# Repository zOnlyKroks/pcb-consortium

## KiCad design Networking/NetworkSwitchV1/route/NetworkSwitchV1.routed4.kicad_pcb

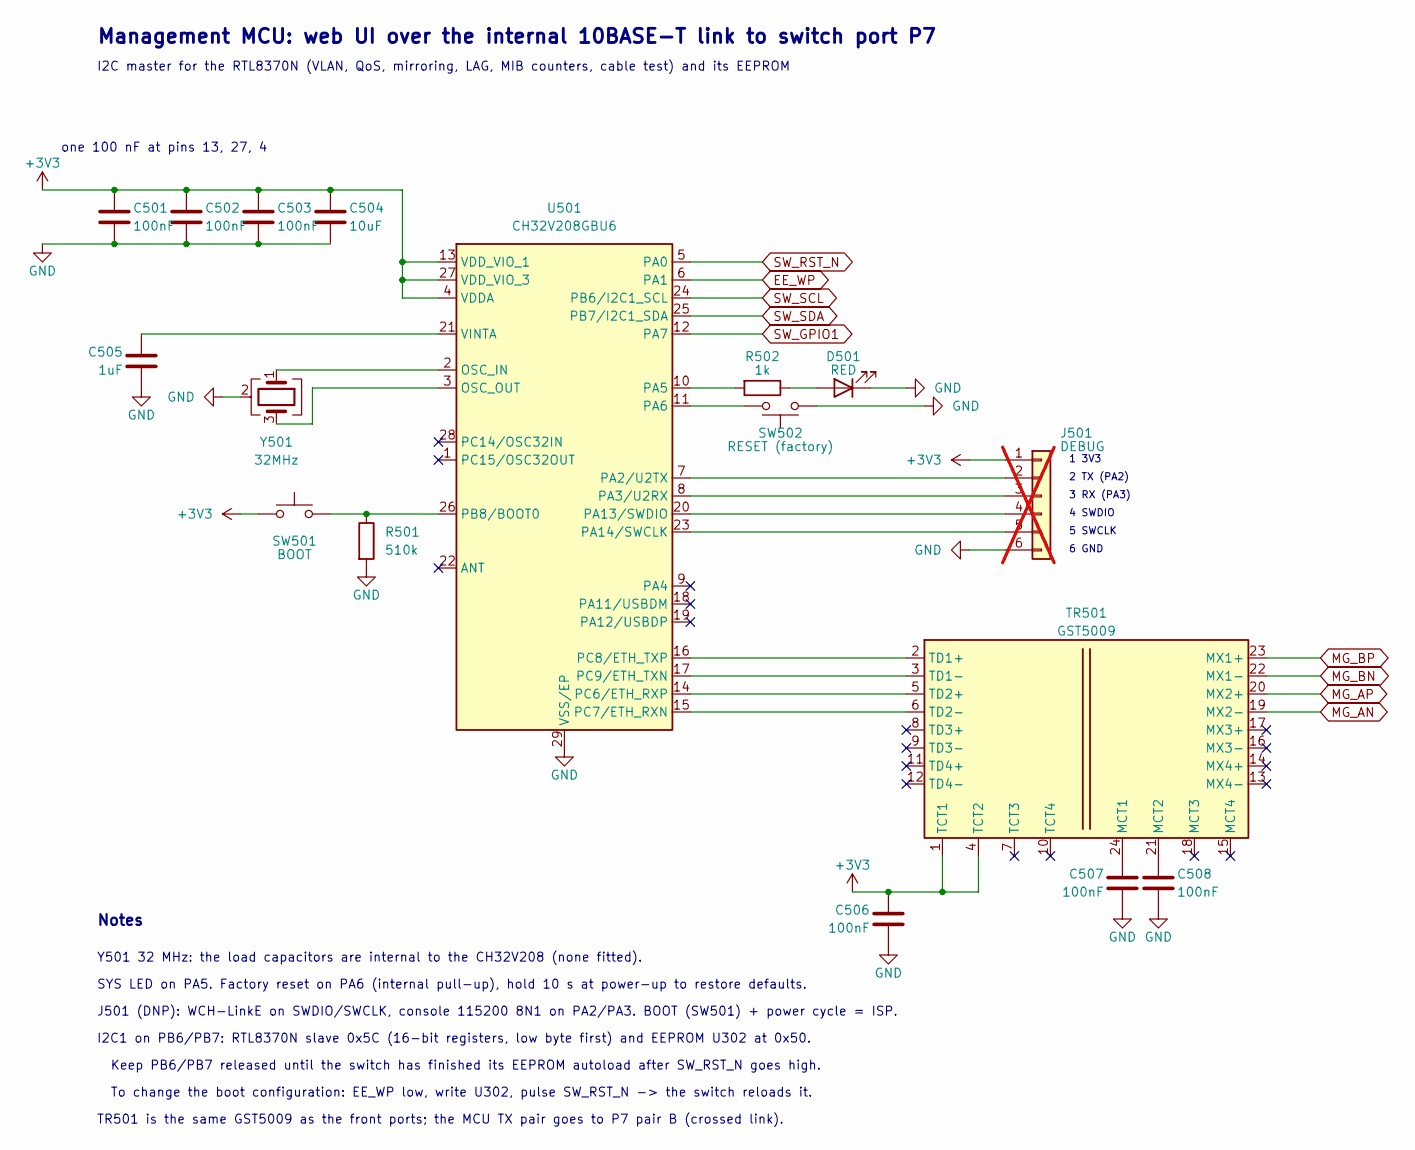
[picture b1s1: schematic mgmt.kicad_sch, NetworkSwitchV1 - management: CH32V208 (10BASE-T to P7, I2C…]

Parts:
C501, C502, C503, C506, C507, C508: 100nF; C_0603_1608Metric; LCSC Part # C14663
C504: 10uF; C_0603_1608Metric; LCSC Part # C19702
C505: 1uF; C_0603_1608Metric; LCSC Part # C15849
D501: RED; LED_0603_1608Metric; LCSC Part # C2286
J501: DEBUG; PinHeader_1x06_P2.54mm_Vertical; LCSC Part # C492405; not fitted
R501: 510k; R_0603_1608Metric; LCSC Part # C23192
R502: 1k; R_0603_1608Metric; LCSC Part # C21190
SW501: BOOT; SW-SMD_4P-L5.1-W5.1-P3.70-LS6.5-TL_H1.5; LCSC Part # C318884
SW502: RESET (factory); SW-SMD_4P-L5.1-W5.1-P3.70-LS6.5-TL_H1.5; LCSC Part # C318884
TR501: GST5009; XFMR-SMD_24P-L15.1-W7.1-P1.00-LS9.7-BL; LCSC Part # C55213474
U501: CH32V208GBU6; QFN-28_L4.0-W4.0-P0.40-BL-EP2.8; LCSC Part # C7434833
Y501: 32MHz; Crystal_SMD_3225-4Pin_3.2x2.5mm; MPN X322532MOB4SI; LCSC Part # C9009

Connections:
+3V3: C501.1, C502.1, C503.1, C504.1, C506.1, J501.1, SW501.1, SW501.2 (1), TR501.1 (TCT1), TR501.4 (TCT2), U501.4 (VDDA), U501.13 (VDD_VIO_1), U501.27 (VDD_VIO_3); also elsewhere on the board
EE_WP: U501.6 (PA1); also elsewhere on the board
GND: C501.2, C502.2, C503.2, C504.2, C505.2, C506.2, C507.2, C508.2, D501.1 (K), J501.6, R501.2, SW502.1, SW502.2 (1), U501.29 (VSS/EP), Y501.2 (G), Y501.4 (G); also elsewhere on the board
MG_AN: TR501.19 (MX2-); also elsewhere on the board
MG_AP: TR501.20 (MX2+); also elsewhere on the board
MG_BN: TR501.22 (MX1-); also elsewhere on the board
MG_BP: TR501.23 (MX1+); also elsewhere on the board
unnamed: D501.2 (A), R502.1
unnamed: J501.2, U501.7 (PA2/U2TX)
unnamed: J501.3, U501.8 (PA3/U2RX)
unnamed: J501.4, U501.20 (PA13/SWDIO)
unnamed: J501.5, U501.23 (PA14/SWCLK)
unnamed: C507.1, TR501.24 (MCT1)
unnamed: C508.1, TR501.21 (MCT2)
unnamed: TR501.2 (TD1+), U501.16 (PC8/ETH_TXP)
unnamed: TR501.3 (TD1-), U501.17 (PC9/ETH_TXN)
unnamed: TR501.5 (TD2+), U501.14 (PC6/ETH_RXP)
unnamed: TR501.6 (TD2-), U501.15 (PC7/ETH_RXN)
unnamed: U501.2 (OSC_IN), Y501.1
unnamed: U501.3 (OSC_OUT), Y501.3
unnamed: R502.2, U501.10 (PA5)
unnamed: SW502.3 (2), SW502.4 (2), U501.11 (PA6)
unnamed: R501.1, SW501.3 (2), SW501.4 (2), U501.26 (PB8/BOOT0)
unnamed: C505.1, U501.21 (VINTA)
SW_GPIO1: U501.12 (PA7); also elsewhere on the board
SW_RST_N: U501.5 (PA0); also elsewhere on the board
SW_SCL: U501.24 (PB6/I2C1_SCL); also elsewhere on the board
SW_SDA: U501.25 (PB7/I2C1_SDA); also elsewhere on the board

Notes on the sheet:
3 RX (PA3)
one 100 nF at pins 13, 27, 4
I2C1 on PB6/PB7: RTL8370N slave 0x5C (16-bit registers, low byte first) and EEPROM U302 at 0x50.
Keep PB6/PB7 released until the switch has finished its EEPROM autoload after SW_RST_N goes high.
Y501 32 MHz: the load capacitors are internal to the CH32V208 (none fitted).
4 SWDIO
Management MCU: web UI over the internal 10BASE-T link to switch port P7
6 GND
J501 (DNP): WCH-LinkE on SWDIO/SWCLK, console 115200 8N1 on PA2/PA3. BOOT (SW501) + power cycle = ISP.
5 SWCLK
TR501 is the same GST5009 as the front ports; the MCU TX pair goes to P7 pair B (crossed link).
To change the boot configuration: EE_WP low, write U302, pulse SW_RST_N -> the switch reloads it.
Notes
SYS LED on PA5. Factory reset on PA6 (internal pull-up), hold 10 s at power-up to restore defaults.
1 3V3
I2C master for the RTL8370N (VLAN, QoS, mirroring, LAG, MIB counters, cable test) and its EEPROM
2 TX (PA2)

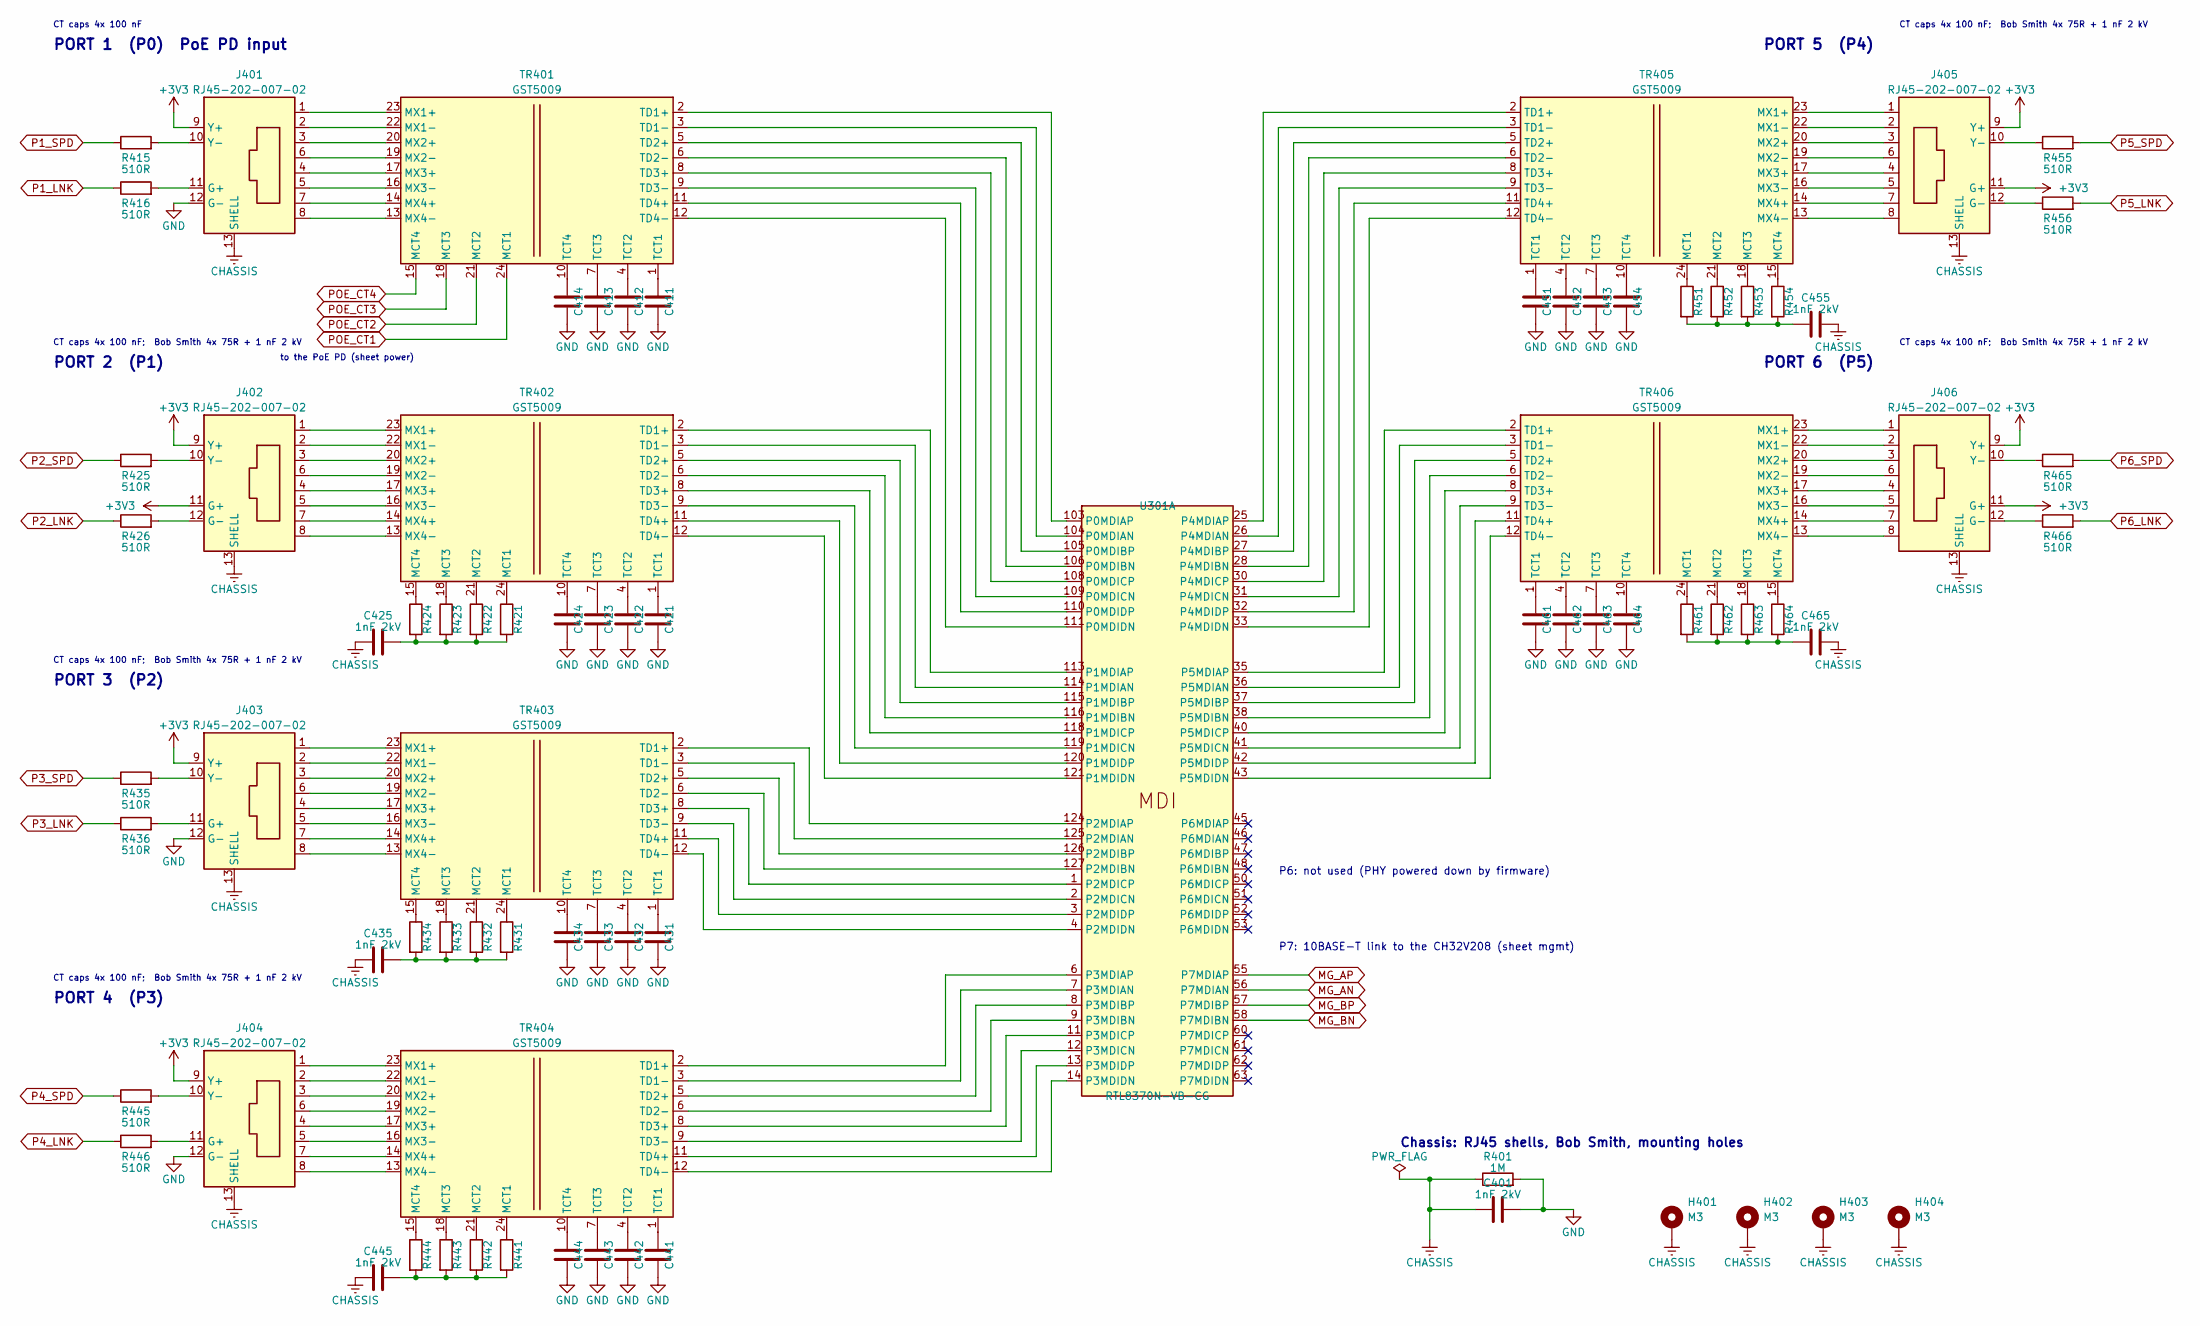
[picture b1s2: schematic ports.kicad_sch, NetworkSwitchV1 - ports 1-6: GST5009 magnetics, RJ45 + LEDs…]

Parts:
C401, C425, C435, C445, C455, C465: 1nF 2kV; C_1206_3216Metric; LCSC Part # C9196
C411, C412, C413, C414, C421, C422, C423, C424, C431, C432, C433, C434, C441, C442, C443, C444, C451, C452, C453, C454, C461, C462, C463, C464: 100nF; C_0603_1608Metric; LCSC Part # C14663
H401, H402, H403, H404: M3; MountingHole_3.2mm_M3_Pad_Via
J401, J402, J403, J404, J405, J406: RJ45-202-007-02; RJ45-TH_RJ45-202-007-02; LCSC Part # C7421418
R401: 1M; R_0603_1608Metric; LCSC Part # C22935
R415, R416, R425, R426, R435, R436, R445, R446, R455, R456, R465, R466: 510R; R_0603_1608Metric; LCSC Part # C23193
R421, R422, R423, R424, R431, R432, R433, R434, R441, R442, R443, R444, R451, R452, R453, R454, R461, R462, R463, R464: 75R; R_0603_1608Metric; LCSC Part # C4275
TR401, TR402, TR403, TR404, TR405, TR406: GST5009; XFMR-SMD_24P-L15.1-W7.1-P1.00-LS9.7-BL; LCSC Part # C55213474
U301: RTL8370N-VB-CG; LQFP-128_L20.0-W14.0-P0.50-BL-EP7.0; LCSC Part # C2803243

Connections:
+3V3: J401.9 (Y+), J402.9 (Y+), J402.11 (G+), J403.9 (Y+), J404.9 (Y+), J405.9 (Y+), J405.11 (G+), J406.9 (Y+), J406.11 (G+); also elsewhere on the board
CHASSIS: C401.1, C425.1, C435.1, C445.1, C455.2, C465.2, H401.1 (1_1), H402.1 (1_1), H403.1 (1_1), H404.1 (1_1), J401.13 (SHELL), J402.13 (SHELL), J403.13 (SHELL), J404.13 (SHELL), J405.13 (SHELL), J406.13 (SHELL), R401.1; also elsewhere on the board
GND: C401.2, C411.2, C412.2, C413.2, C414.2, C421.2, C422.2, C423.2, C424.2, C431.2, C432.2, C433.2, C434.2, C441.2, C442.2, C443.2, C444.2, C451.2, C452.2, C453.2, C454.2, C461.2, C462.2, C463.2, C464.2, J401.12 (G-), J403.12 (G-), J404.12 (G-), R401.2; also elsewhere on the board
MG_AN: U301.56 (P7MDIAN); also elsewhere on the board
MG_AP: U301.55 (P7MDIAP); also elsewhere on the board
MG_BN: U301.58 (P7MDIBN); also elsewhere on the board
MG_BP: U301.57 (P7MDIBP); also elsewhere on the board
unnamed: C425.2, R421.2, R422.2, R423.2, R424.2
unnamed: C435.2, R431.2, R432.2, R433.2, R434.2
unnamed: C445.2, R441.2, R442.2, R443.2, R444.2
unnamed: C455.1, R451.2, R452.2, R453.2, R454.2
unnamed: C465.1, R461.2, R462.2, R463.2, R464.2
unnamed: J401.11 (G+), R416.2
unnamed: J401.10 (Y-), R415.2
unnamed: J402.12 (G-), R426.2
unnamed: J402.10 (Y-), R425.2
unnamed: J403.11 (G+), R436.2
unnamed: J403.10 (Y-), R435.2
unnamed: J404.11 (G+), R446.2
unnamed: J404.10 (Y-), R445.2
unnamed: J405.12 (G-), R456.1
unnamed: J405.10 (Y-), R455.1
unnamed: J406.12 (G-), R466.1
unnamed: J406.10 (Y-), R465.1
unnamed: J401.1, TR401.23 (MX1+)
unnamed: J401.2, TR401.22 (MX1-)
unnamed: J401.3, TR401.20 (MX2+)
unnamed: J401.6, TR401.19 (MX2-)
unnamed: J401.4, TR401.17 (MX3+)
unnamed: J401.5, TR401.16 (MX3-)
unnamed: J401.7, TR401.14 (MX4+)
unnamed: J401.8, TR401.13 (MX4-)
unnamed: C411.1, TR401.1 (TCT1)
unnamed: C412.1, TR401.4 (TCT2)
unnamed: C413.1, TR401.7 (TCT3)
unnamed: C414.1, TR401.10 (TCT4)
unnamed: TR401.2 (TD1+), U301.103 (P0MDIAP)
unnamed: TR401.3 (TD1-), U301.104 (P0MDIAN)
unnamed: TR401.5 (TD2+), U301.105 (P0MDIBP)
unnamed: TR401.6 (TD2-), U301.106 (P0MDIBN)
unnamed: TR401.8 (TD3+), U301.108 (P0MDICP)
unnamed: TR401.9 (TD3-), U301.109 (P0MDICN)
unnamed: TR401.11 (TD4+), U301.110 (P0MDIDP)
unnamed: TR401.12 (TD4-), U301.111 (P0MDIDN)
unnamed: R421.1, TR402.24 (MCT1)
unnamed: R422.1, TR402.21 (MCT2)
unnamed: R423.1, TR402.18 (MCT3)
unnamed: R424.1, TR402.15 (MCT4)
unnamed: J402.1, TR402.23 (MX1+)
unnamed: J402.2, TR402.22 (MX1-)
unnamed: J402.3, TR402.20 (MX2+)
unnamed: J402.6, TR402.19 (MX2-)
unnamed: J402.4, TR402.17 (MX3+)
unnamed: J402.5, TR402.16 (MX3-)
unnamed: J402.7, TR402.14 (MX4+)
unnamed: J402.8, TR402.13 (MX4-)
unnamed: C421.1, TR402.1 (TCT1)
unnamed: C422.1, TR402.4 (TCT2)
unnamed: C423.1, TR402.7 (TCT3)
unnamed: C424.1, TR402.10 (TCT4)
unnamed: TR402.2 (TD1+), U301.113 (P1MDIAP)
unnamed: TR402.3 (TD1-), U301.114 (P1MDIAN)
unnamed: TR402.5 (TD2+), U301.115 (P1MDIBP)
unnamed: TR402.6 (TD2-), U301.116 (P1MDIBN)
unnamed: TR402.8 (TD3+), U301.118 (P1MDICP)
unnamed: TR402.9 (TD3-), U301.119 (P1MDICN)
unnamed: TR402.11 (TD4+), U301.120 (P1MDIDP)
unnamed: TR402.12 (TD4-), U301.121 (P1MDIDN)
unnamed: R431.1, TR403.24 (MCT1)
unnamed: R432.1, TR403.21 (MCT2)
unnamed: R433.1, TR403.18 (MCT3)
unnamed: R434.1, TR403.15 (MCT4)
unnamed: J403.1, TR403.23 (MX1+)
unnamed: J403.2, TR403.22 (MX1-)
unnamed: J403.3, TR403.20 (MX2+)
unnamed: J403.6, TR403.19 (MX2-)
unnamed: J403.4, TR403.17 (MX3+)
unnamed: J403.5, TR403.16 (MX3-)
unnamed: J403.7, TR403.14 (MX4+)
unnamed: J403.8, TR403.13 (MX4-)
unnamed: C431.1, TR403.1 (TCT1)
unnamed: C432.1, TR403.4 (TCT2)
unnamed: C433.1, TR403.7 (TCT3)
unnamed: C434.1, TR403.10 (TCT4)
unnamed: TR403.2 (TD1+), U301.124 (P2MDIAP)
unnamed: TR403.3 (TD1-), U301.125 (P2MDIAN)
unnamed: TR403.5 (TD2+), U301.126 (P2MDIBP)
unnamed: TR403.6 (TD2-), U301.127 (P2MDIBN)
unnamed: TR403.8 (TD3+), U301.1 (P2MDICP)
unnamed: TR403.9 (TD3-), U301.2 (P2MDICN)
unnamed: TR403.11 (TD4+), U301.3 (P2MDIDP)
unnamed: TR403.12 (TD4-), U301.4 (P2MDIDN)
unnamed: R441.1, TR404.24 (MCT1)
unnamed: R442.1, TR404.21 (MCT2)
unnamed: R443.1, TR404.18 (MCT3)
unnamed: R444.1, TR404.15 (MCT4)
unnamed: J404.1, TR404.23 (MX1+)
unnamed: J404.2, TR404.22 (MX1-)
unnamed: J404.3, TR404.20 (MX2+)
unnamed: J404.6, TR404.19 (MX2-)
unnamed: J404.4, TR404.17 (MX3+)
unnamed: J404.5, TR404.16 (MX3-)
unnamed: J404.7, TR404.14 (MX4+)
unnamed: J404.8, TR404.13 (MX4-)
unnamed: C441.1, TR404.1 (TCT1)
unnamed: C442.1, TR404.4 (TCT2)
unnamed: C443.1, TR404.7 (TCT3)
unnamed: C444.1, TR404.10 (TCT4)
unnamed: TR404.2 (TD1+), U301.6 (P3MDIAP)
unnamed: TR404.3 (TD1-), U301.7 (P3MDIAN)
unnamed: TR404.5 (TD2+), U301.8 (P3MDIBP)
unnamed: TR404.6 (TD2-), U301.9 (P3MDIBN)
unnamed: TR404.8 (TD3+), U301.11 (P3MDICP)
unnamed: TR404.9 (TD3-), U301.12 (P3MDICN)
unnamed: TR404.11 (TD4+), U301.13 (P3MDIDP)
unnamed: TR404.12 (TD4-), U301.14 (P3MDIDN)
unnamed: R451.1, TR405.24 (MCT1)
unnamed: R452.1, TR405.21 (MCT2)
unnamed: R453.1, TR405.18 (MCT3)
unnamed: R454.1, TR405.15 (MCT4)
unnamed: J405.1, TR405.23 (MX1+)
unnamed: J405.2, TR405.22 (MX1-)
unnamed: J405.3, TR405.20 (MX2+)
unnamed: J405.6, TR405.19 (MX2-)
unnamed: J405.4, TR405.17 (MX3+)
unnamed: J405.5, TR405.16 (MX3-)
unnamed: J405.7, TR405.14 (MX4+)
unnamed: J405.8, TR405.13 (MX4-)
unnamed: C451.1, TR405.1 (TCT1)
unnamed: C452.1, TR405.4 (TCT2)
unnamed: C453.1, TR405.7 (TCT3)
unnamed: C454.1, TR405.10 (TCT4)
unnamed: TR405.2 (TD1+), U301.25 (P4MDIAP)
unnamed: TR405.3 (TD1-), U301.26 (P4MDIAN)
unnamed: TR405.5 (TD2+), U301.27 (P4MDIBP)
unnamed: TR405.6 (TD2-), U301.28 (P4MDIBN)
unnamed: TR405.8 (TD3+), U301.30 (P4MDICP)
unnamed: TR405.9 (TD3-), U301.31 (P4MDICN)
unnamed: TR405.11 (TD4+), U301.32 (P4MDIDP)
unnamed: TR405.12 (TD4-), U301.33 (P4MDIDN)
unnamed: R461.1, TR406.24 (MCT1)
unnamed: R462.1, TR406.21 (MCT2)
unnamed: R463.1, TR406.18 (MCT3)
unnamed: R464.1, TR406.15 (MCT4)
unnamed: J406.1, TR406.23 (MX1+)
unnamed: J406.2, TR406.22 (MX1-)
unnamed: J406.3, TR406.20 (MX2+)
unnamed: J406.6, TR406.19 (MX2-)
unnamed: J406.4, TR406.17 (MX3+)
unnamed: J406.5, TR406.16 (MX3-)
unnamed: J406.7, TR406.14 (MX4+)
unnamed: J406.8, TR406.13 (MX4-)
unnamed: C461.1, TR406.1 (TCT1)
unnamed: C462.1, TR406.4 (TCT2)
unnamed: C463.1, TR406.7 (TCT3)
unnamed: C464.1, TR406.10 (TCT4)
unnamed: TR406.2 (TD1+), U301.35 (P5MDIAP)
unnamed: TR406.3 (TD1-), U301.36 (P5MDIAN)
unnamed: TR406.5 (TD2+), U301.37 (P5MDIBP)
unnamed: TR406.6 (TD2-), U301.38 (P5MDIBN)
unnamed: TR406.8 (TD3+), U301.40 (P5MDICP)
unnamed: TR406.9 (TD3-), U301.41 (P5MDICN)
unnamed: TR406.11 (TD4+), U301.42 (P5MDIDP)
unnamed: TR406.12 (TD4-), U301.43 (P5MDIDN)
P1_LNK: R416.1; also elsewhere on the board
P1_SPD: R415.1; also elsewhere on the board
P2_LNK: R426.1; also elsewhere on the board
P2_SPD: R425.1; also elsewhere on the board
P3_LNK: R436.1; also elsewhere on the board
P3_SPD: R435.1; also elsewhere on the board
P4_LNK: R446.1; also elsewhere on the board
P4_SPD: R445.1; also elsewhere on the board
P5_LNK: R456.2; also elsewhere on the board
P5_SPD: R455.2; also elsewhere on the board
P6_LNK: R466.2; also elsewhere on the board
P6_SPD: R465.2; also elsewhere on the board
POE_CT1: TR401.24 (MCT1); also elsewhere on the board
POE_CT2: TR401.21 (MCT2); also elsewhere on the board
POE_CT3: TR401.18 (MCT3); also elsewhere on the board
POE_CT4: TR401.15 (MCT4); also elsewhere on the board

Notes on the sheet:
PORT 4 (P3)
CT caps 4x 100 nF; Bob Smith 4x 75R + 1 nF 2 kV
PORT 3 (P2)
CT caps 4x 100 nF
PORT 1 (P0) PoE PD input
PORT 2 (P1)
Chassis: RJ45 shells, Bob Smith, mounting holes
to the PoE PD (sheet power)
PORT 6 (P5)
P6: not used (PHY powered down by firmware)
P7: 10BASE-T link to the CH32V208 (sheet mgmt)
PORT 5 (P4)

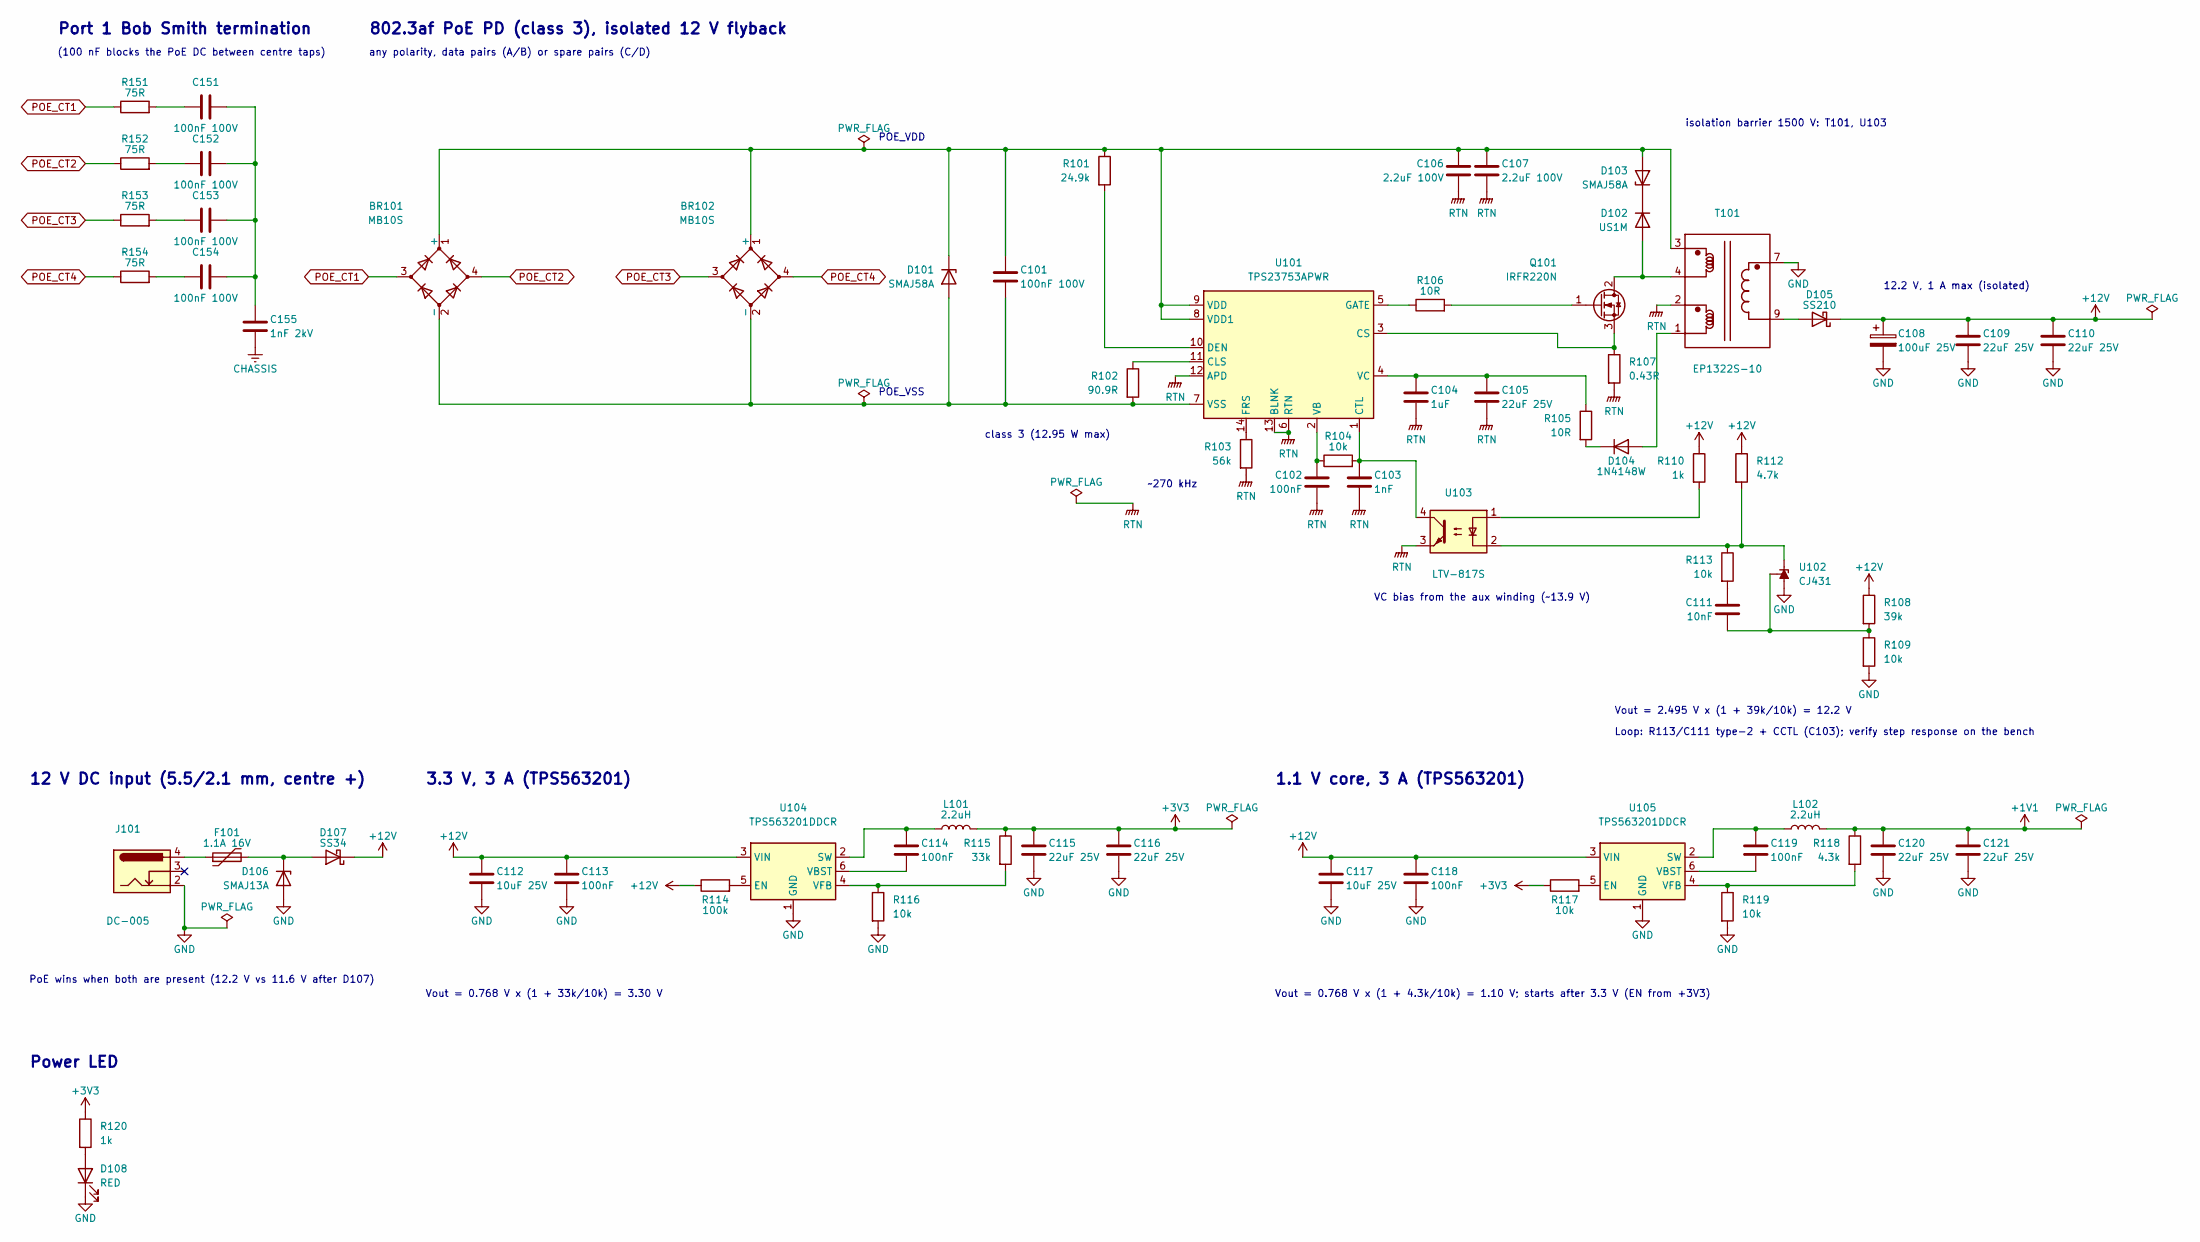
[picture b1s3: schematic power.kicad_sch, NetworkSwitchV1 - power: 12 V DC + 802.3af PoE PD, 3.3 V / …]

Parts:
BR101, BR102: MB10S; MBS_L4.7-W3.8-P2.40-LS7.0-TL; LCSC Part # C2488
C101, C151, C152, C153, C154: 100nF 100V; C_0805_2012Metric; LCSC Part # C28233
C102, C113, C114, C118, C119: 100nF; C_0603_1608Metric; LCSC Part # C14663
C103: 1nF; C_0603_1608Metric; LCSC Part # C1588
C104: 1uF; C_0603_1608Metric; LCSC Part # C15849
C105, C109, C110, C115, C116, C120, C121: 22uF 25V; C_0805_2012Metric; LCSC Part # C45783
C106, C107: 2.2uF 100V; C_1210_3225Metric; LCSC Part # C55151
C108: 100uF 25V; CP_Elec_6.3x7.7; LCSC Part # C970685
C111: 10nF; C_0603_1608Metric; LCSC Part # C57112
C112, C117: 10uF 25V; C_0805_2012Metric; LCSC Part # C15850
C155: 1nF 2kV; C_1206_3216Metric; LCSC Part # C9196
D101, D103: SMAJ58A; D_SMA; LCSC Part # C123816
D102: US1M; D_SMA; LCSC Part # C412437
D104: 1N4148W; D_SOD-123; LCSC Part # C81598
D105: SS210; D_SMA; LCSC Part # C14996
D106: SMAJ13A; D_SMA; LCSC Part # C10764
D107: SS34; D_SMA; LCSC Part # C8678
D108: RED; LED_0603_1608Metric; LCSC Part # C2286
F101: 1.1A 16V; Fuse_1206_3216Metric; LCSC Part # C7542961
J101: DC-005; DC-IN-TH_DC-005-5.5-2.0; LCSC Part # C16214
L101, L102: 2.2uH; IND-SMD_L4.0-W4.0_FNR40XXS; LCSC Part # C167869
Q101: IRFR220N; TO-252-2_L6.6-W6.1-P4.57-LS9.9-BR-CW; Rating 200 V 8 A; LCSC Part # C22365390
R101: 24.9k; R_0603_1608Metric; LCSC Part # C25962
R102: 90.9R; R_0603_1608Metric; LCSC Part # C23130
R103: 56k; R_0603_1608Metric; LCSC Part # C23206
R104, R109, R113, R116, R117, R119: 10k; R_0603_1608Metric; LCSC Part # C25804
R105, R106: 10R; R_0603_1608Metric; LCSC Part # C22859
R107: 0.43R; R_1206_3216Metric; LCSC Part # C24965
R108: 39k; R_0603_1608Metric; LCSC Part # C23153
R110, R120: 1k; R_0603_1608Metric; LCSC Part # C21190
R112: 4.7k; R_0603_1608Metric; LCSC Part # C23162
R114: 100k; R_0603_1608Metric; LCSC Part # C25803
R115: 33k; R_0603_1608Metric; LCSC Part # C4216
R118: 4.3k; R_0603_1608Metric; LCSC Part # C23159
R151, R152, R153, R154: 75R; R_0603_1608Metric; LCSC Part # C4275
T101: EP1322S-10; XFMR-SMD_EP1322S-10; LCSC Part # C37328796
U101: TPS23753APWR; TSSOP-14_L5.0-W4.4-P0.65-LS6.4-BL; LCSC Part # C92115
U102: CJ431; SOT-23-3_L2.9-W1.6-P1.90-LS2.8-BR; LCSC Part # C3113
U103: LTV-817S; OPTO-SMD-4_L4.6-W6.5-P2.54-LS10.3-BL; LCSC Part # C109227
U104, U105: TPS563201DDCR; TSOT-23-6; LCSC Part # C116592

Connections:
+1V1: C120.1, C121.1, L102.2, R118.1; also elsewhere on the board
+3V3: C115.1, C116.1, L101.2, R115.1, R117.1, R120.1; also elsewhere on the board
+12V: C108.1, C109.1, C110.1, C112.1, C113.1, C117.1, C118.1, D105.1 (K), D107.1 (K), R108.1, R110.1, R112.1, R114.1, U104.3 (VIN), U105.3 (VIN)
CHASSIS: C155.2; also elsewhere on the board
GND: C108.2, C109.2, C110.2, C112.2, C113.2, C115.2, C116.2, C117.2, C118.2, C120.2, C121.2, D106.2 (A), D108.1 (K), J101.2, R109.2, R116.2, R119.2, T101.7, T101.8, U102.3 (A), U104.1 (GND), U105.1 (GND); also elsewhere on the board
unnamed: BR101.1 (+), BR102.1 (+), C101.1, C106.1, C107.1, D101.1 (K), D103.2 (A), R101.1, T101.3, U101.8 (VDD1), U101.9 (VDD)
unnamed: BR101.2 (-), BR102.2 (-), C101.2, D101.2 (A), R102.2, U101.7 (VSS)
unnamed: C111.1, R113.2
unnamed: C151.1, R151.2
unnamed: C151.2, C152.2, C153.2, C154.2, C155.1
unnamed: C152.1, R152.2
unnamed: C153.1, R153.2
unnamed: C154.1, R154.2
unnamed: D102.2 (A), Q101.2 (D), T101.4
unnamed: D102.1 (K), D103.1 (K)
unnamed: D104.2 (A), T101.1
unnamed: D104.1 (K), R105.2
unnamed: D105.2 (A), T101.9, T101.10
unnamed: D106.1 (K), D107.2 (A), F101.2
unnamed: D108.2 (A), R120.2
unnamed: F101.1, J101.4
unnamed: Q101.1 (G), R106.2
unnamed: Q101.3 (S), R107.1, U101.3 (CS)
unnamed: R110.2, U103.1
unnamed: R102.1, U101.11 (CLS)
unnamed: C103.1, R104.2, U101.1 (CTL), U103.4
unnamed: R101.2, U101.10 (DEN)
unnamed: R103.1, U101.14 (FRS)
unnamed: R106.1, U101.5 (GATE)
unnamed: C102.1, R104.1, U101.2 (VB)
unnamed: C104.1, C105.1, R105.1, U101.4 (VC)
unnamed: R112.2, R113.1, U102.2 (K), U103.2
unnamed: C111.2, R108.2, R109.1, U102.1 (REF)
unnamed: R114.2, U104.5 (EN)
unnamed: C114.1, L101.1, U104.2 (SW)
unnamed: C114.2, U104.6 (VBST)
unnamed: R115.2, R116.1, U104.4 (VFB)
unnamed: R117.2, U105.5 (EN)
unnamed: C119.1, L102.1, U105.2 (SW)
unnamed: C119.2, U105.6 (VBST)
unnamed: R118.2, R119.1, U105.4 (VFB)
POE_CT1: BR101.3, R151.1; also elsewhere on the board
POE_CT2: BR101.4, R152.1; also elsewhere on the board
POE_CT3: BR102.3, R153.1; also elsewhere on the board
POE_CT4: BR102.4, R154.1; also elsewhere on the board
RTN: C102.2, C103.2, C104.2, C105.2, C106.2, C107.2, R103.2, R107.2, T101.2, U101.6 (RTN), U101.12 (APD), U101.13 (BLNK), U103.3

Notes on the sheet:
any polarity, data pairs (A/B) or spare pairs (C/D)
3.3 V, 3 A (TPS563201)
Vout = 2.495 V x (1 + 39k/10k) = 12.2 V
~270 kHz
class 3 (12.95 W max)
Port 1 Bob Smith termination
Loop: R113/C111 type-2 + CCTL (C103); verify step response on the bench
802.3af PoE PD (class 3), isolated 12 V flyback
POE_VDD
VC bias from the aux winding (~13.9 V)
1.1 V core, 3 A (TPS563201)
12.2 V, 1 A max (isolated)
Vout = 0.768 V x (1 + 33k/10k) = 3.30 V
POE_VSS
Vout = 0.768 V x (1 + 4.3k/10k) = 1.10 V; starts after 3.3 V (EN from +3V3)
isolation barrier 1500 V: T101, U103
(100 nF blocks the PoE DC between centre taps)
Power LED
12 V DC input (5.5/2.1 mm, centre +)
PoE wins when both are present (12.2 V vs 11.6 V after D107)

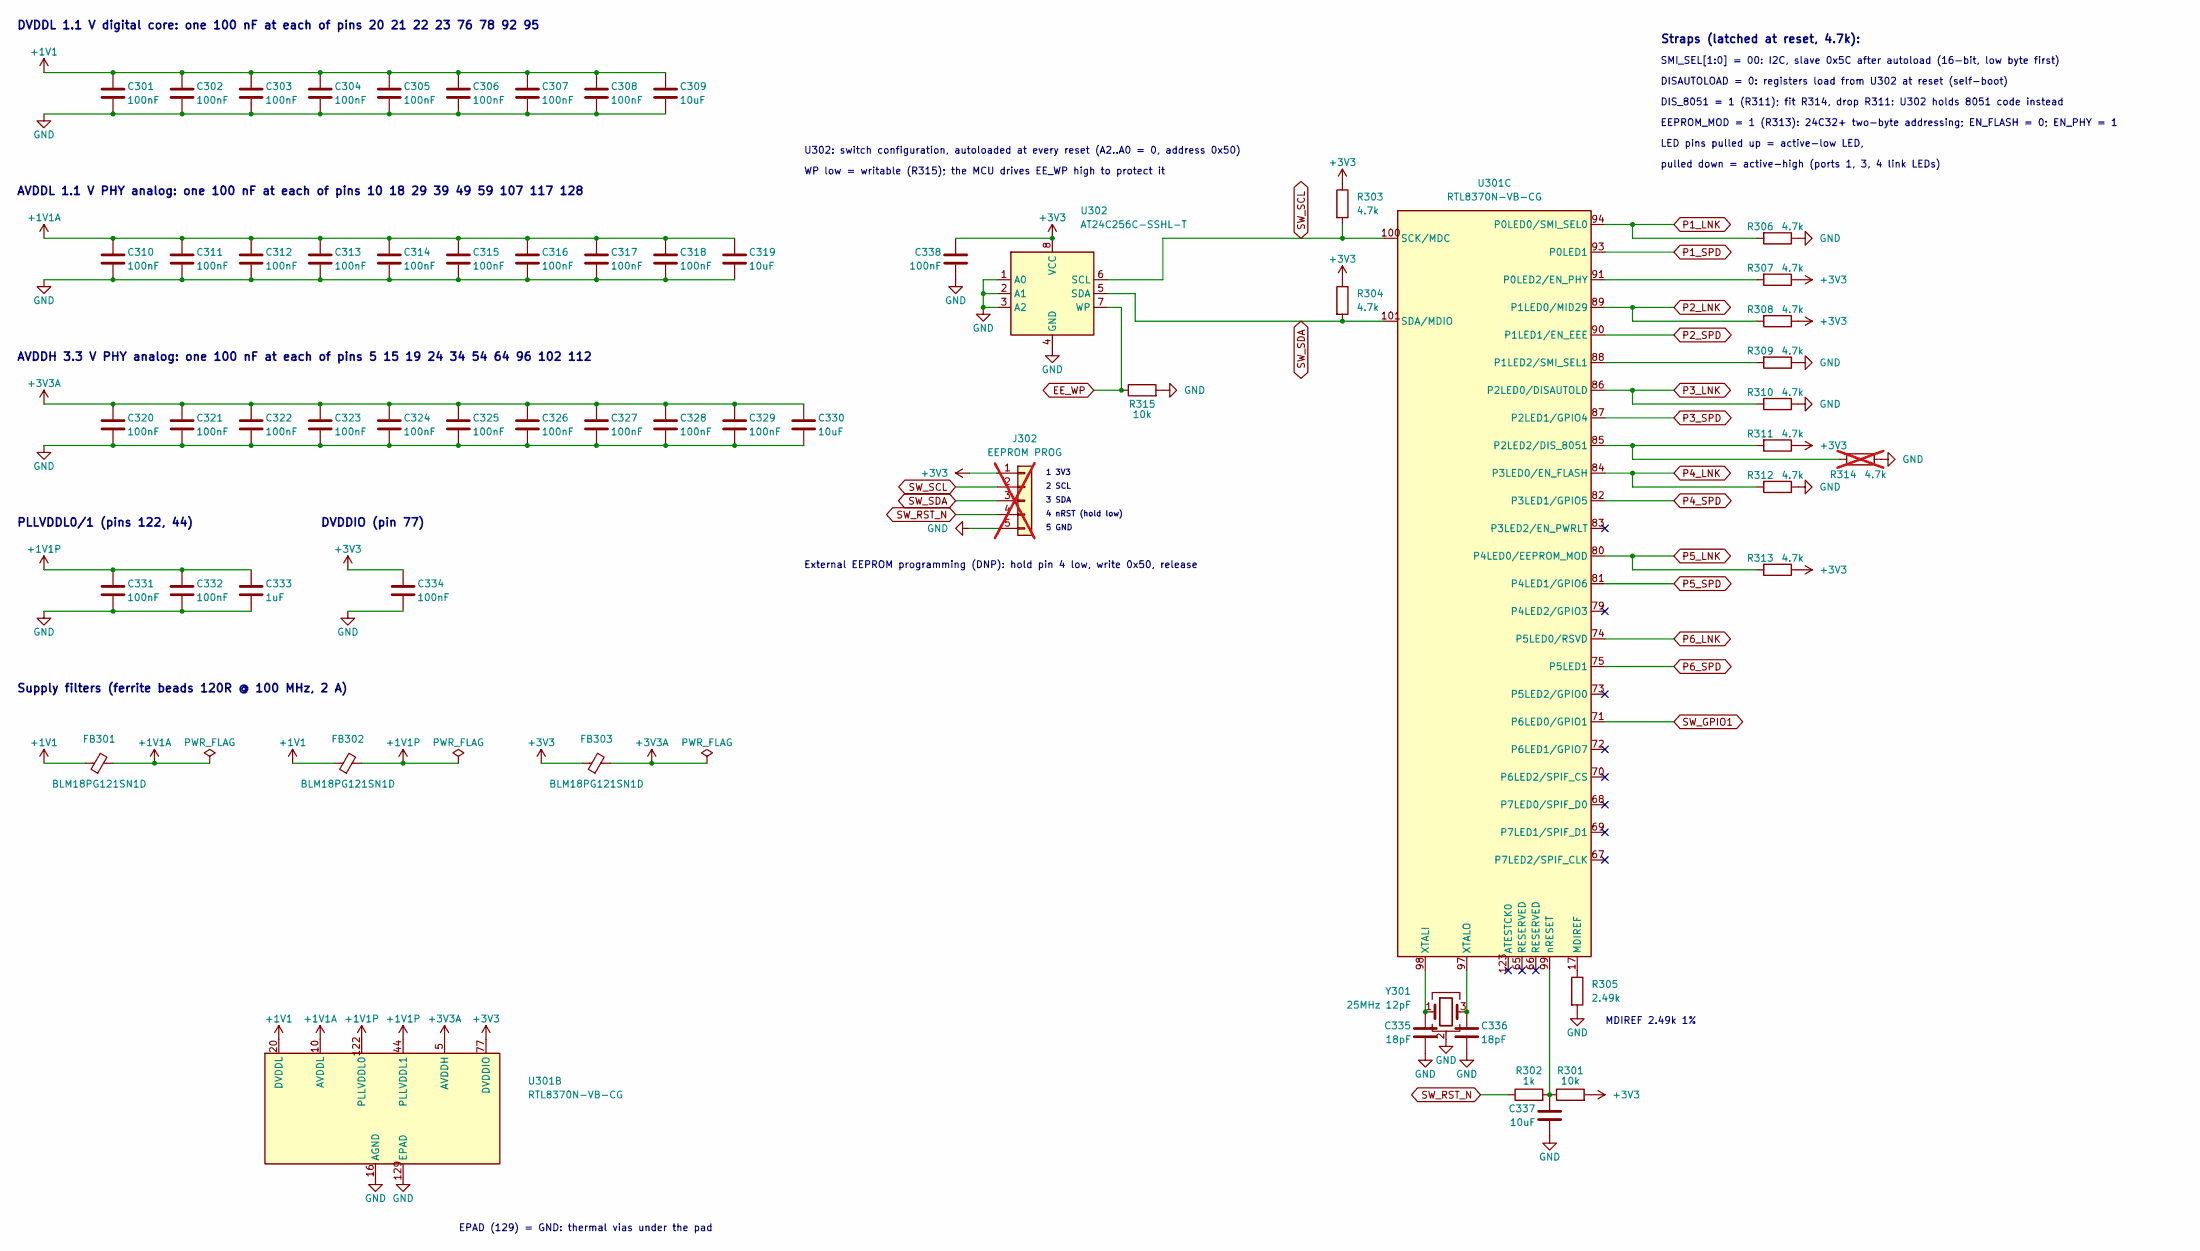
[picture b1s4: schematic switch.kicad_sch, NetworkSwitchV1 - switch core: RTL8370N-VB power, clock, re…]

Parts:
C301, C302, C303, C304, C305, C306, C307, C308, C310, C311, C312, C313, C314, C315, C316, C317, C318, C320, C321, C322, C323, C324, C325, C326, C327, C328, C329, C331, C332, C334, C338: 100nF; C_0603_1608Metric; LCSC Part # C14663
C309, C319, C330, C337: 10uF; C_0603_1608Metric; LCSC Part # C19702
C333: 1uF; C_0603_1608Metric; LCSC Part # C15849
C335, C336: 18pF; C_0603_1608Metric; LCSC Part # C1647
FB301, FB302, FB303: BLM18PG121SN1D; L_0603_1608Metric; LCSC Part # C14709
J302: EEPROM PROG; PinHeader_1x05_P2.54mm_Vertical; LCSC Part # C492404; not fitted
R301, R315: 10k; R_0603_1608Metric; LCSC Part # C25804
R302: 1k; R_0603_1608Metric; LCSC Part # C21190
R303, R304, R306, R307, R308, R309, R310, R311, R312, R313: 4.7k; R_0603_1608Metric; LCSC Part # C23162
R305: 2.49k; R_0603_1608Metric; LCSC Part # C22908
R314: 4.7k; R_0603_1608Metric; LCSC Part # C23162; not fitted
U301: RTL8370N-VB-CG; LQFP-128_L20.0-W14.0-P0.50-BL-EP7.0; LCSC Part # C2803243
U302: AT24C256C-SSHL-T; SOIC-8_3.9x4.9mm_P1.27mm; LCSC Part # C6482
Y301: 25MHz 12pF; Crystal_SMD_3225-4Pin_3.2x2.5mm; MPN X322525MOB4SI; LCSC Part # C9006

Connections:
+1V1: C301.1, C302.1, C303.1, C304.1, C305.1, C306.1, C307.1, C308.1, C309.1, FB301.1, FB302.1, U301.20 (DVDDL), U301.21 (DVDDL), U301.22 (DVDDL), U301.23 (DVDDL), U301.76 (DVDDL), U301.78 (DVDDL), U301.92 (DVDDL), U301.95 (DVDDL); also elsewhere on the board
+1V1A: C310.1, C311.1, C312.1, C313.1, C314.1, C315.1, C316.1, C317.1, C318.1, C319.1, FB301.2, U301.10 (AVDDL), U301.18 (AVDDL), U301.29 (AVDDL), U301.39 (AVDDL), U301.49 (AVDDL), U301.59 (AVDDL), U301.107 (AVDDL), U301.117 (AVDDL), U301.128 (AVDDL)
+1V1P: C331.1, C332.1, C333.1, FB302.2, U301.44 (PLLVDDL1), U301.122 (PLLVDDL0)
+3V3: C334.1, C338.1, FB303.1, J302.1, R301.2, R303.1, R304.1, R307.1, R308.1, R311.1, R313.1, U301.77 (DVDDIO), U302.8 (VCC); also elsewhere on the board
+3V3A: C320.1, C321.1, C322.1, C323.1, C324.1, C325.1, C326.1, C327.1, C328.1, C329.1, C330.1, FB303.2, U301.5 (AVDDH), U301.15 (AVDDH), U301.19 (AVDDH), U301.24 (AVDDH), U301.34 (AVDDH), U301.54 (AVDDH), U301.64 (AVDDH), U301.96 (AVDDH), U301.102 (AVDDH), U301.112 (AVDDH)
EE_WP: R315.1, U302.7 (WP); also elsewhere on the board
GND: C301.2, C302.2, C303.2, C304.2, C305.2, C306.2, C307.2, C308.2, C309.2, C310.2, C311.2, C312.2, C313.2, C314.2, C315.2, C316.2, C317.2, C318.2, C319.2, C320.2, C321.2, C322.2, C323.2, C324.2, C325.2, C326.2, C327.2, C328.2, C329.2, C330.2, C331.2, C332.2, C333.2, C334.2, C335.2, C336.2, C337.2, C338.2, J302.5, R305.2, R306.1, R309.1, R310.1, R312.1, R314.1, R315.2, U301.16 (AGND), U301.129 (EPAD), U302.1 (A0), U302.2 (A1), U302.3 (A2), U302.4 (GND), Y301.2 (G), Y301.4 (G); also elsewhere on the board
unnamed: R305.1, U301.17 (MDIREF)
unnamed: R307.2, U301.91 (P0LED2/EN_PHY)
unnamed: R309.2, U301.88 (P1LED2/SMI_SEL1)
unnamed: R311.2, R314.2, U301.85 (P2LED2/DIS_8051)
unnamed: C335.1, U301.98 (XTALI), Y301.1
unnamed: C336.1, U301.97 (XTALO), Y301.3
unnamed: C337.1, R301.1, R302.2, U301.99 (nRESET)
P1_LNK: R306.2, U301.94 (P0LED0/SMI_SEL0); also elsewhere on the board
P1_SPD: U301.93 (P0LED1); also elsewhere on the board
P2_LNK: R308.2, U301.89 (P1LED0/MID29); also elsewhere on the board
P2_SPD: U301.90 (P1LED1/EN_EEE); also elsewhere on the board
P3_LNK: R310.2, U301.86 (P2LED0/DISAUTOLD); also elsewhere on the board
P3_SPD: U301.87 (P2LED1/GPIO4); also elsewhere on the board
P4_LNK: R312.2, U301.84 (P3LED0/EN_FLASH); also elsewhere on the board
P4_SPD: U301.82 (P3LED1/GPIO5); also elsewhere on the board
P5_LNK: R313.2, U301.80 (P4LED0/EEPROM_MOD); also elsewhere on the board
P5_SPD: U301.81 (P4LED1/GPIO6); also elsewhere on the board
P6_LNK: U301.74 (P5LED0/RSVD); also elsewhere on the board
P6_SPD: U301.75 (P5LED1); also elsewhere on the board
SW_GPIO1: U301.71 (P6LED0/GPIO1); also elsewhere on the board
SW_RST_N: J302.4, R302.1; also elsewhere on the board
SW_SCL: J302.2, R303.2, U301.100 (SCK/MDC), U302.6 (SCL); also elsewhere on the board
SW_SDA: J302.3, R304.2, U301.101 (SDA/MDIO), U302.5 (SDA); also elsewhere on the board

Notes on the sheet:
DVDDIO (pin 77)
DVDDL 1.1 V digital core: one 100 nF at each of pins 20 21 22 23 76 78 92 95
1 3V3
Supply filters (ferrite beads 120R @ 100 MHz, 2 A)
DIS_8051 = 1 (R311); fit R314, drop R311: U302 holds 8051 code instead
LED pins pulled up = active-low LED,
AVDDL 1.1 V PHY analog: one 100 nF at each of pins 10 18 29 39 49 59 107 117 128
EPAD (129) = GND: thermal vias under the pad
Straps (latched at reset, 4.7k):
5 GND
PLLVDDL0/1 (pins 122, 44)
U302: switch configuration, autoloaded at every reset (A2..A0 = 0, address 0x50)
SMI_SEL[1:0] = 00: I2C, slave 0x5C after autoload (16-bit, low byte first)
MDIREF 2.49k 1%
pulled down = active-high (ports 1, 3, 4 link LEDs)
AVDDH 3.3 V PHY analog: one 100 nF at each of pins 5 15 19 24 34 54 64 96 102 112
External EEPROM programming (DNP): hold pin 4 low, write 0x50, release
WP low = writable (R315); the MCU drives EE_WP high to protect it
DISAUTOLOAD = 0: registers load from U302 at reset (self-boot)
3 SDA
EEPROM_MOD = 1 (R313): 24C32+ two-byte addressing; EN_FLASH = 0; EN_PHY = 1
4 nRST (hold low)
2 SCL
